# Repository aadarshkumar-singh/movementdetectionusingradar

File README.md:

# movementdetectionusingradar
The system driven hardware design to detect movements using a 24 GHz Doppler radar sensor.

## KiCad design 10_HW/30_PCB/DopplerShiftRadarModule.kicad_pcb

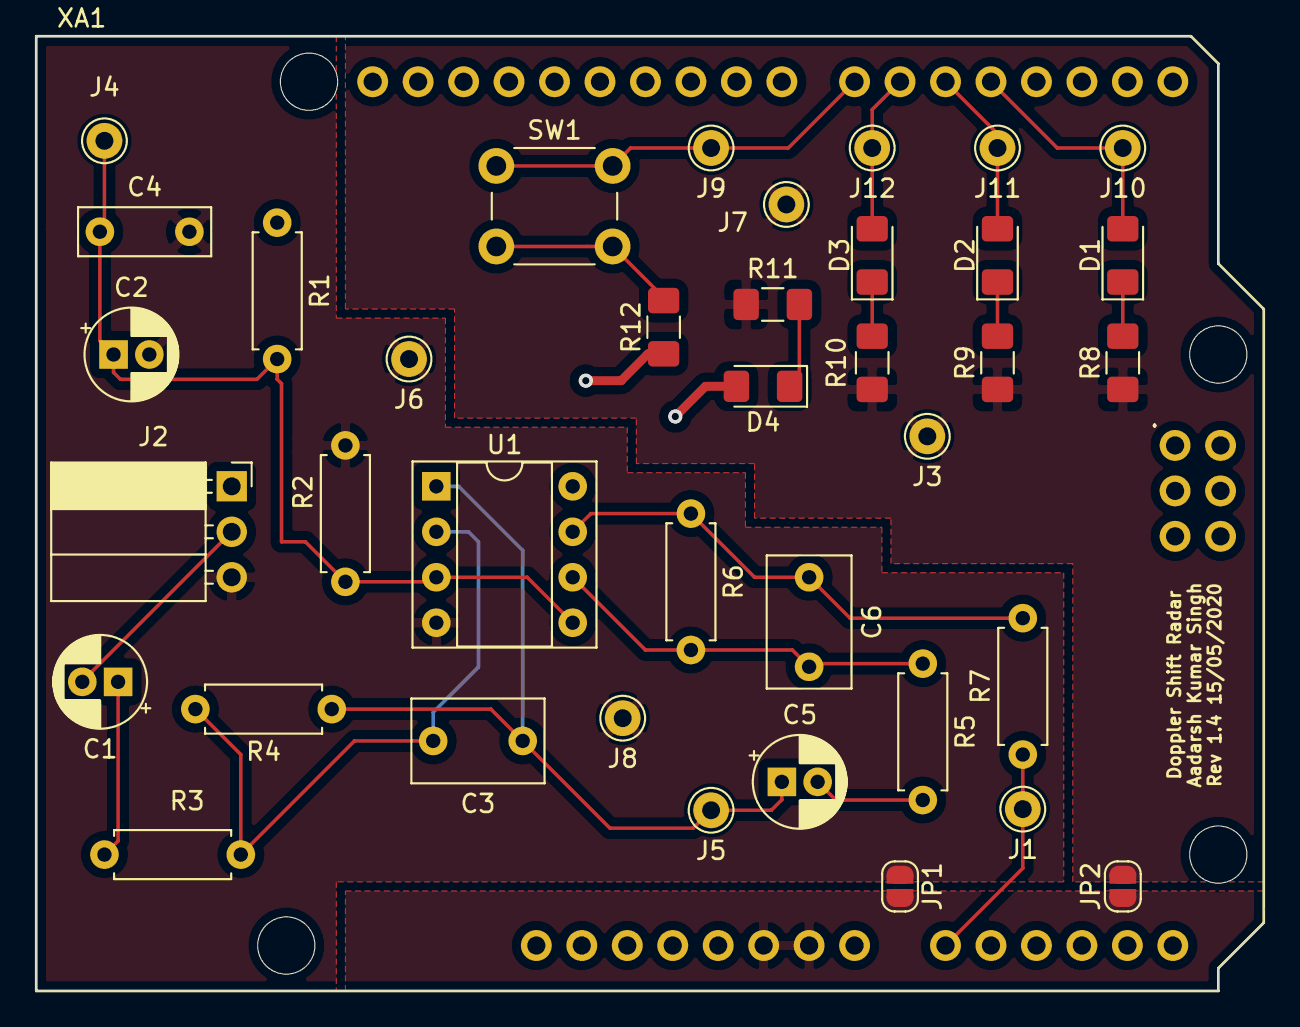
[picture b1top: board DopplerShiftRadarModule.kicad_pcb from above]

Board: 4 copper layers, 68.6 x 53.3 mm, 39 parts (0 on the bottom side), 22 nets.

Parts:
C1, C5: 4.7u; CP_Radial_D5.0mm_P2.00mm
C2: 22u; CP_Radial_D5.0mm_P2.00mm
C3: 1.5n; C_Rect_L7.2mm_W4.5mm_P5.00mm_FKS2_FKP2_MKS2_MKP2
C4: 100n; C_Rect_L7.2mm_W2.5mm_P5.00mm_FKS2_FKP2_MKS2_MKP2
C6: 3.3n; C_Rect_L7.2mm_W4.5mm_P5.00mm_FKS2_FKP2_MKS2_MKP2
D1: LED green; LED_1206_3216Metric_Pad1.42x1.75mm_HandSolder
D2: LED yellow; LED_1206_3216Metric_Pad1.42x1.75mm_HandSolder
D3, D4: LED red; LED_1206_3216Metric_Pad1.42x1.75mm_HandSolder
J1: FILTER_2; Pin_D1.0mm_L10.0mm
J2: Radar; PinSocket_1x03_P2.54mm_Horizontal
J3, J7: TP_GNDD; Pin_D1.0mm_L10.0mm
J4: TP_VCM; Pin_D1.0mm_L10.0mm
J5: FILTER_1; Pin_D1.0mm_L10.0mm
J6, J8: TP_GNDA; Pin_D1.0mm_L10.0mm
J9: TP_BUTTON; Pin_D1.0mm_L10.0mm
J10: TP_LED_G; Pin_D1.0mm_L10.0mm
J11: TP_LED_Y; Pin_D1.0mm_L10.0mm
J12: TP_LED_R; Pin_D1.0mm_L10.0mm
JP1: GNDA_JOIN; SolderJumper-2_P1.3mm_Open_RoundedPad1.0x1.5mm
JP2: GNDD_JOIN; SolderJumper-2_P1.3mm_Open_RoundedPad1.0x1.5mm
R1, R2: 1k; R_Axial_DIN0207_L6.3mm_D2.5mm_P7.62mm_Horizontal
R3, R5: 2.2k; R_Axial_DIN0207_L6.3mm_D2.5mm_P7.62mm_Horizontal
R4: 220k; R_Axial_DIN0207_L6.3mm_D2.5mm_P7.62mm_Horizontal
R6: 100k; R_Axial_DIN0207_L6.3mm_D2.5mm_P7.62mm_Horizontal
R7: 100; R_Axial_DIN0207_L6.3mm_D2.5mm_P7.62mm_Horizontal
R8, R9, R10, R11, R12: 220; R_1206_3216Metric_Pad1.42x1.75mm_HandSolder
SW1: SW_Push; SW_PUSH_6mm_H4.3mm
U1: LM358; DIP-8_W7.62mm_Socket
XA1: Uno_Shield; Arduino_Uno_Shield

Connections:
/LEDGREEN: D1.2, J10.1, XA1.D4
/LEDRED: D3.2, J12.1, XA1.D6
/LEDYELLOW: D2.2, J11.1, XA1.D5
/PUSHBUTTON: J9.1, SW1.1, XA1.D7
/VIN: C1.2, J2.2
/VOUT: J1.1, R7.1, XA1.A0
GND: JP1.2, JP2.1, XA1.GND2, XA1.GND3
GNDA: C2.2, C4.2, J2.3, J6.1, J8.1, JP1.1, R2.2, U1.4
GNDD: J3.1, J7.1, JP2.2, R8.1, R9.1, R10.1, R11.2
unnamed: C1.1, R3.2
unnamed: C2.1, C4.1, J4.1, R1.2, R2.1, U1.3, U1.5
unnamed: C3.1, C5.1, J5.1, R4.1, U1.1
unnamed: C3.2, R3.1, R4.2, U1.2
unnamed: C5.2, R5.2
unnamed: C6.1, R6.1, R7.2, U1.7
unnamed: C6.2, R5.1, R6.2, U1.6
unnamed: D1.1, R8.2
unnamed: D2.1, R9.2
unnamed: D3.1, R10.2
unnamed: D4.1, R11.1
unnamed: R12.2, SW1.2
VCC: D4.2, J2.1, R1.1, R12.1, U1.8, XA1.5V1

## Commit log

2021-11-08 The system driven hardware design to detect movements using using a 24 GHz Doppler radar sensor.
